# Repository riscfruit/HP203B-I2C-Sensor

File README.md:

# HP203N-I2C-sensor
Riscfruit HP203N I2C sensor module, measuring barometric pressure and temperature.

### Software
For Micropython or Circuitpython, we have released [HP203B-Library](https://github.com/riscfruit/HP203B-Library).

### Gallery

### License
Copyright (c) 2026, Riscfruit Laboratory. This open source hardware is released under [CERN-OHL-S-2.0](LICENSE).

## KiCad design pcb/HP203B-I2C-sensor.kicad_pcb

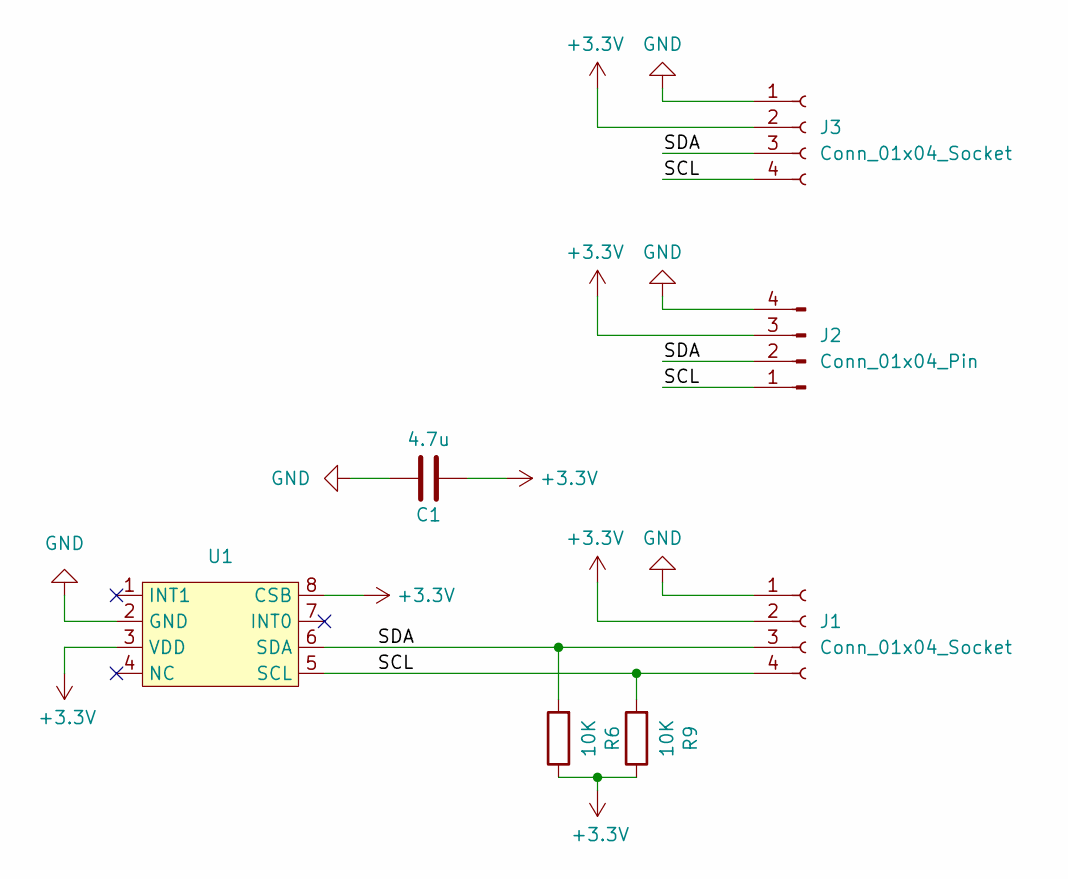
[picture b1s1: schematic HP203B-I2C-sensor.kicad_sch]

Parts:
C1: 4.7u; C_0402_1005Metric
J1, J3: Conn_01x04_Socket; JST_SH_SM04B-SRSS-TB_1x04-1MP_P1.00mm_Horizontal
J2: Conn_01x04_Pin; PinHeader_1x04_P2.54mm_Vertical
R6, R9: 10K; R_0402_1005Metric
U1: QFN-8_HP203B

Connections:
+3.3V: C1.1, J1.2, J2.3, J3.2, R6.1, R9.1, U1.3 (VDD), U1.8 (CSB)
/SCL: J1.4, J2.1, J3.4, R9.2, U1.5 (SCL)
/SDA: J1.3, J2.2, J3.3, R6.2, U1.6 (SDA)
GND: C1.2, J1.1, J2.4, J3.1, U1.2 (GND)

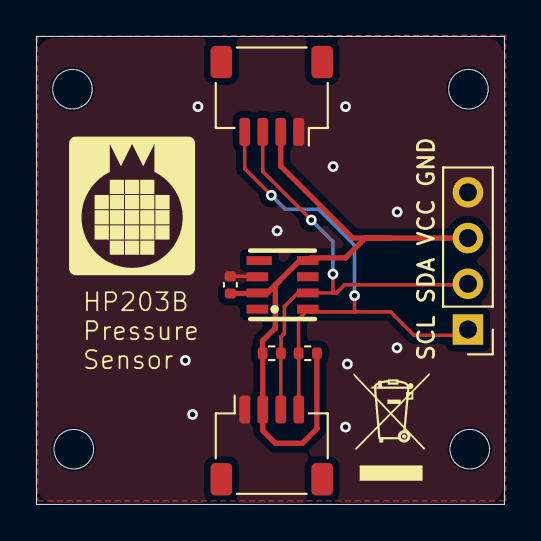
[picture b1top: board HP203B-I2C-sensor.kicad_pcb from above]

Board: 2 copper layers, 26.0 x 26.0 mm, 11 parts (0 on the bottom side), 4 nets.

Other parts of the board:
H1, H1#2, H1#3, H1#4: MountingHole; MountingHole_2.2mm_M2
